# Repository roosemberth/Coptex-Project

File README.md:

Coptex Project Source
==========================

Coptex Project Git Repostory

Developer: Roosemberth Palacios - Email: roosemberth@gmail.com

==========================

Coptex Project concept is building a Helicopter Capable of full understanding of it's physical environment and adapt in a Dynamic way to ensure full space position control and displace in an efficient manner within it's surroundings.

'Scorpion Copter' Is the name of the main device, Running an AI Engine for Human Interaction, Route Planning, Collision-Avoidance (ACRP: Anti-Collision Route Planner)

Coptex Project it's been developped over a Cutting-Edge Platform (Samsung's exynos5422 SoC) with a fairy complex Multicore Processing, Embedding 4 Cortex A7 Processors for System Static Load and 4 Cortex A15 for System Real-Time Artificial Intelligence tasks, Mali-T628 GPU for GPGPU-Programming model with OpenCL.

*Scorpion Copter Will be equipped with 2 HD Cameras to provice stereo-vision and Power a Telemetry Engine.
*In the mechanical part, It will probably be printed in Titanium and/or Carbon Nanotubes Structures.
*High Speed Networking Capabilities WiFi (802.11b/g; 25Mbps), GSM, 3G (7.2Mbps) Interface.
*Ecryted Security Protocols (SSL, SELinux).
*In Case of Emergency Protocols, Restore a Secure Shell If Connection gets Compromised.
*Dynamic Magnetic Suspension
*Full Inertial-Spatial-Pose Control
*Worst-Case Scenario Recovering System

Actual Stage is From Planning to First Prototype

Best Regards!

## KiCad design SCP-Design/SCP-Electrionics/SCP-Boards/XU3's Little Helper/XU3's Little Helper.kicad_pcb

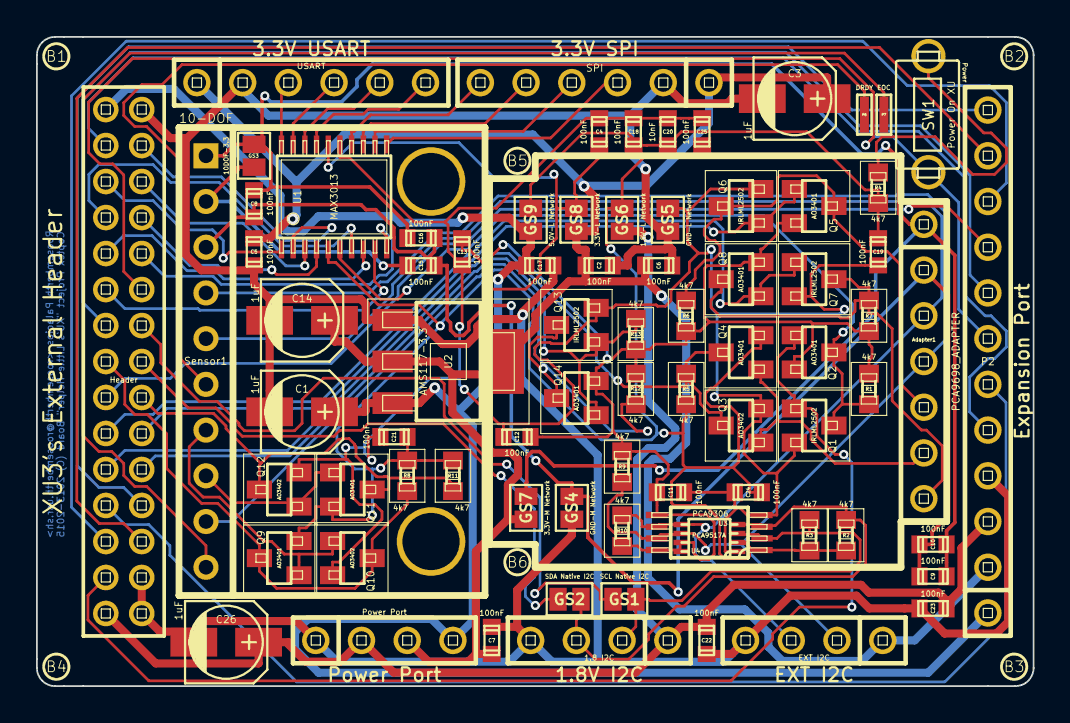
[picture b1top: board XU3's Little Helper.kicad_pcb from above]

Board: 2 copper layers, 55.4 x 36.1 mm, 85 parts (0 on the bottom side), 58 nets.

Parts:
1.8 I2C: 1.8V I2C; pinhead-1X04
 : Bird chip logo
Adapter1: PCA9698_ADAPTER; pinhead-1X07
B1, B2, B3, B4, B5, B6: O; 1pin
C1, C3, C14, C26: 1uF; c_elec_4x4.5
C2, C4, C5, C6, C7, C8, C9, C10, C11, C12, C13, C15, C16, C17, C18, C19, C21, C22, C23, C24, C25: 100nF; c_0603
C20: 10nF; c_0603
EXT I2C: EXT I2C; pinhead-1X04
GS1: SCL Native I2C; GS2
GS2: SDA Native I2C; GS2
GS3: 10DOF-3.3; GS2
GS4: GND-M Network; GS2
GS5: GND-L Network; GS2
GS6: 1.8V-L Network; GS2
GS7: 3.3V-M Network; GS2
GS8: 3.3V-L Network; GS2
GS9: 5.0V-L Network; GS2
Header: XU3's External Header; pinhead-2X15M
P2: Expansion Port; pinhead-1X12
P6: DRDY; pinhead-1X01
P7: EOC; pinhead-1X01
Power Port: Power Port; pinhead-1X04
Q1, Q6, Q7, Q13: IRLML2502; -SOT23
Q2, Q4, Q5, Q8, Q9, Q11, Q14: AO3401; -SOT23
Q3, Q10, Q12: AO3402; -SOT23
R1, R2, R3, R4, R5, R6, R7, R8, R9, R10, R11, R12, R13: 4k7; -R0603
SPI: 3.3V SPI; pinhead-1X06
SW1: Power On XU; switch-misc-FSM
Sensor1: 10-DOF
U1: MAX3013; -TSSOP20
U2: AMS117-3.3; -SOT223
U3: PCA9306; -TSSOP8
U4: PCA9517A; -TSSOP8
USART: 3.3V USART; pinhead-1X06

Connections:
/1.8 I2C SCL: 1.8 I2C.2, GS1.1, R3.2, U3.3, U4.2
/1.8 I2C SDA: 1.8 I2C.3, GS2.2, R2.2, U3.4, U4.3
/1.8V: C21.1, C24.1, C25.1, GS6.1, Q4.2, Q9.2, Q11.2, R2.1, R3.1, R5.2, R8.2, R11.2, U1.5, U3.2, U4.1
/1.8V=H: 1.8 I2C.1, C22.1, C23.1, C26.1, GS6.2, Header.29, P2.3, Power Port.2
/3.3V: C4.1, C11.1, C12.1, C13.1, GS8.1, Q2.2, Q5.2, Q8.2, Q14.2, R1.2, R6.1, R7.1, R9.2, R10.1, R12.1, R13.2, U1.16, U3.7, U3.8, U4.5, U4.8
/3.3V=H: C2.1, C3.1, C5.1, C6.1, C7.1, C14.1, EXT I2C.1, GS7.2, GS8.2, P2.2, Power Port.3, SPI.1, U2.2, U2.4, USART.1
/3.3V=M: Adapter1.1, C8.1, C9.1, C10.1, C16.2, GS3.2, GS7.1, Sensor1.1
/5.0V: C18.1, C19.1, C20.1, GS9.1, R4.1
/5.0V=H: C1.1, C17.1, GS9.2, Header.1, P2.1, Power Port.4, U2.3
/ADC0.AIN1: Header.3, P2.5
/ADC0.AIN3: Header.23, P2.6
/GND: C4.2, C11.2, C12.2, C13.2, C18.2, C19.2, C20.2, C21.2, C24.2, C25.2, GS5.1, Q1.2, Q3.2, Q6.2, Q7.2, Q10.2, Q12.2, Q13.2, U1.15, U3.1, U4.4
/GND=H: 1.8 I2C.4, C1.2, C2.2, C3.2, C5.2, C6.2, C7.2, C14.2, C17.2, C22.2, C23.2, C26.2, EXT I2C.4, GS4.2, GS5.2, Header.2, Header.28, Header.30, P2.4, Power Port.1, SPI.2, U2.1, USART.2
/GND=M: Adapter1.2, C8.2, C9.2, C10.2, C15.2, C16.1, GS4.1, Sensor1.3
/MAX3013_Enable: Header.27, Q1.1, Q2.1
/Native I2C SCL: GS1.2, Header.14
/Native I2C SDA: GS2.1, Header.16
/PCA9698 IRQ: Header.21, Q3.3, Q4.3, R5.1
/PCA9698 OE: Header.19, Q7.1, Q8.1
/PCA9698 RESET: Header.20, Q5.1, Q6.1
/SCL: Adapter1.4, EXT I2C.2, R9.1, Sensor1.4, U3.6, U4.7
/SDA: Adapter1.3, EXT I2C.3, R10.2, Sensor1.5, U3.5, U4.6
/XE13: Header.13, P2.8
/XE14: Header.17, P2.9
/XE15: Header.25, P2.10
/XE16: Header.26, P2.11
/XE17: Header.24, P2.12
/XU PWRON: Header.12, P2.7, SW1.2
/~AccelIRQ: Header.15, Q9.3, Q10.3, R8.1
/~GyroIRQ: Header.18, Q11.3, Q12.3, R11.1
/~PSReset: Header.22, Q13.1, Q14.1, R13.1
unnamed: Adapter1.5, Q5.3, Q6.3, R6.2
unnamed: Adapter1.6, Q3.1, Q4.1
unnamed: Adapter1.7, Q7.3, Q8.3, R7.2
unnamed: C15.1, GS3.1, Sensor1.2
unnamed: U1.20, USART.3
unnamed: U1.19, USART.4
unnamed: U1.18, USART.5
unnamed: U1.17, USART.6
unnamed: Header.4, U1.2
unnamed: Header.5, U1.1
unnamed: Header.6, U1.3
unnamed: Header.7, U1.7
unnamed: Header.8, U1.4
unnamed: Header.9, U1.8
unnamed: Header.10, U1.10
unnamed: Header.11, U1.9
unnamed: SPI.3, U1.11
unnamed: SPI.4, U1.12
unnamed: SPI.5, U1.13
unnamed: SPI.6, U1.14
unnamed: P6.1, Sensor1.6
unnamed: P7.1, Sensor1.10
unnamed: Q1.3, Q2.3, R1.1, U1.6
unnamed: Q9.1, Q10.1, Sensor1.7
unnamed: Q11.1, Q12.1, Sensor1.8
unnamed: Q13.3, Q14.3, R12.2, Sensor1.9
unnamed: R4.2, SW1.1

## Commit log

2014-07-14 Initial Push
2014-07-14 Playing with Root Makefile
2014-07-14 Added (folked from hardkernel/linux -b odroid-3.13.y-linaro) kernel sources and .gitignore file
2014-07-15 Fixing SCP-Kernel Submodule Issue
2014-07-15 Fixing SCP-Kernel Submodule Issues
2014-07-15 Moving SCP-Platform/SCP-Kernel to a new folked repo
2014-07-15 Added New SCP-Kernel Submodule
2014-07-16 Playing with Makefiles
2014-07-16 Compiled Kernel
2014-07-16 Renamed Scheduler file. TODO: Implement HwCtrl Class
2014-07-16 Azulejo-Main-Engine, xu-local, Coptex-Project-Dev Correspond to Remote Locations and Main Branch Name
2014-07-16 Moving from misleading location
2014-08-07 Working on HwCtrl Namespace, Errors on SCP-HwCtrl Source and Header files on sharing HwCtrl Namespace. Deleted Scheduler Source and Header files. Code was pulled to main HwCtrl Files, may be put back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
2014-08-07 Working on HwCtrl Namespace, Errors on SCP-HwCtrl Source and Header files on sharing HwCtrl Namespace. Deleted Scheduler Source and Header files. Code was pulled to main HwCtrl Files, may be put back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
2014-08-07 Fixed Namespaces Issue.
2014-08-09 Working on Gyroscope Class Code
    Done SCP-HwCtrl.cpp Optimizations
    Done I2C-Bus Header and Source files
    I2C Class Includes Write and Send Functions
    and Initialization Requires I2C Dev File as Argument
2014-08-09 Temporally Done with Gyroscope Class, almost all methods have been implemented except "bool SCP-HwCtrl::IMU::Gyroscope::config(void *ConfigPacket)" An error-notifying system needs to be implemented i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
    Side Notes: Changed from boost::numeric::ublas to eigen3 Linear Algebra
    Library
2014-08-10 Temporally Done with Accelerometer Class, almost all methods have been implemented except "bool SCP-HwCtrl::IMU::Accelerometer::config(void *ConfigPacket)" An error-notifying system needs to be imple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
    Side Notes: Fixed TODO-list Tracking Importance Missing Tags
2014-08-11 Temporally Done with Magnetometer Class, almost all methods have been implemented except "bool SCP-HwCtrl::IMU::Magnetometer::config(void *ConfigPacket)" An error-notifying system needs to be impleme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
    Side Notes: Fixed Gravity Constants in SCP-Config.h
2014-08-12 Temporally Done with Barometer Class Definition. Implementation remains to prior check. Data get algorithm proposed by datasheet seems unnecessary complicated. Needs futher study
    Implementation Pending
2014-08-12 Added TODO String
2014-08-23 Changing from XU to XU3 on Main Platform, Main reason is new GPU (ARM Mali, Open Source) and HMP Samsung's Solution, Providing What the original Platform was supposed to (8 Paralel Cores Running, Ope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
2014-08-26 Updated Kernel, moved Kernel Modules to drivers/Coptex/, see Submodule Commit for More Information
2014-09-01 Added Mali SDKs to tools
2014-11-22 Working on IMU:
    Modified in order to be used as a stand-alone header-only library
2014-11-26 Ported IMU-Related Code from C++ to C. (Almost) Ready to be ported to Linux Kernel. Missing <float> type handling.

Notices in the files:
SCP-Design/SCP-Electrionics/SCP-Boards/XU3's Little Helper/XU3's Little Helper.kicad_pcb:
Coptex Project (C) 2013-2015
Coptex Project \"XU's Little Helper\" Board (C) 2013-2015
